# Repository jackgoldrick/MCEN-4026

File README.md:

# MCEN-4026
Manufacturing my pain and suffering

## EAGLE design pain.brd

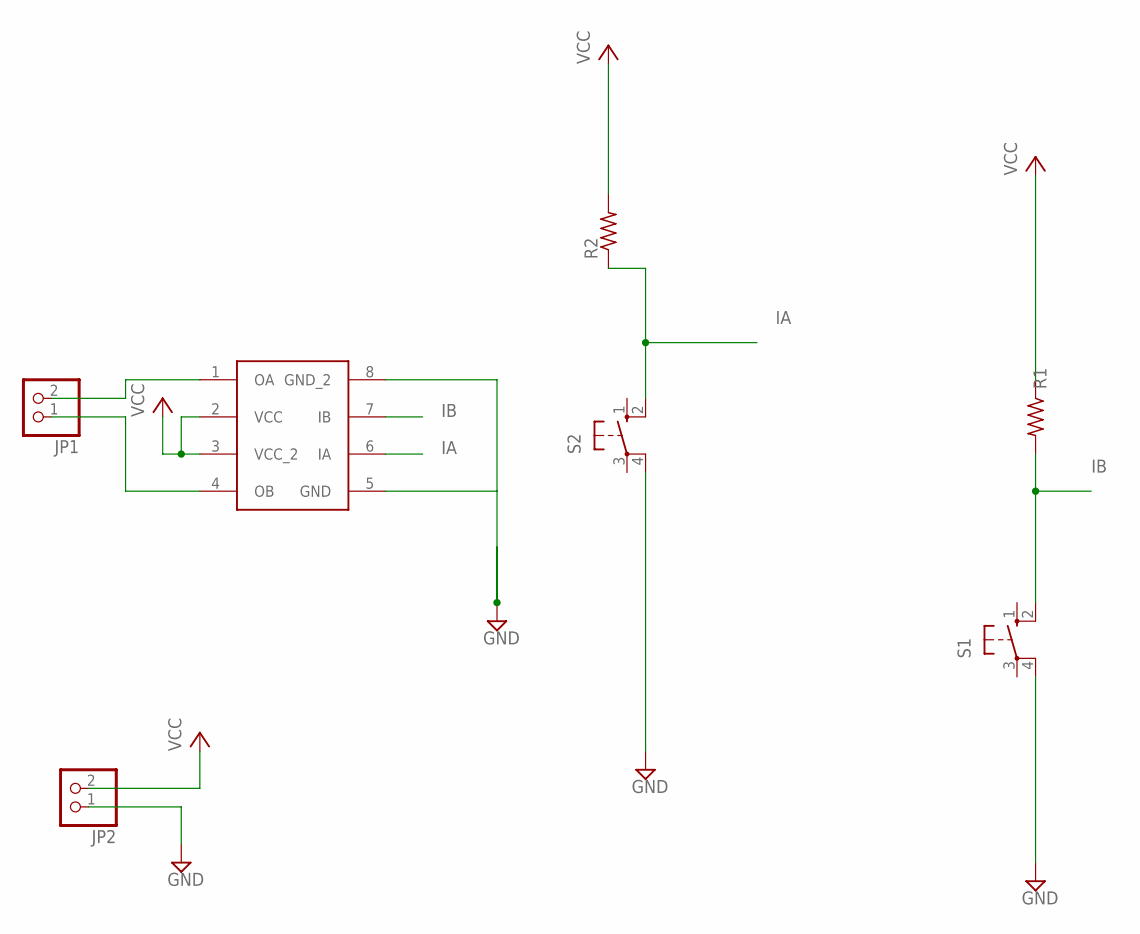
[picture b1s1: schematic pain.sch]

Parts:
JP1, JP2: PINHD-1X2; 1X02
R1, R2: R-US_R0603; R0603
S1, S2: 40-XX; B3F-40XX
U$1: L9110; DIP8

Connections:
GND: JP2.1, S1.4 (P1), S2.4 (P1), U$1.5 (GND), U$1.8 (GND_2)
IA: R2.1, S2.2 (S1), U$1.6 (IA)
IB: R1.2, S1.2 (S1), U$1.7 (IB)
unnamed: JP1.1, U$1.4 (OB)
unnamed: JP1.2, U$1.1 (OA)
VCC: JP2.2, R1.1, R2.2, U$1.2 (VCC), U$1.3 (VCC_2)

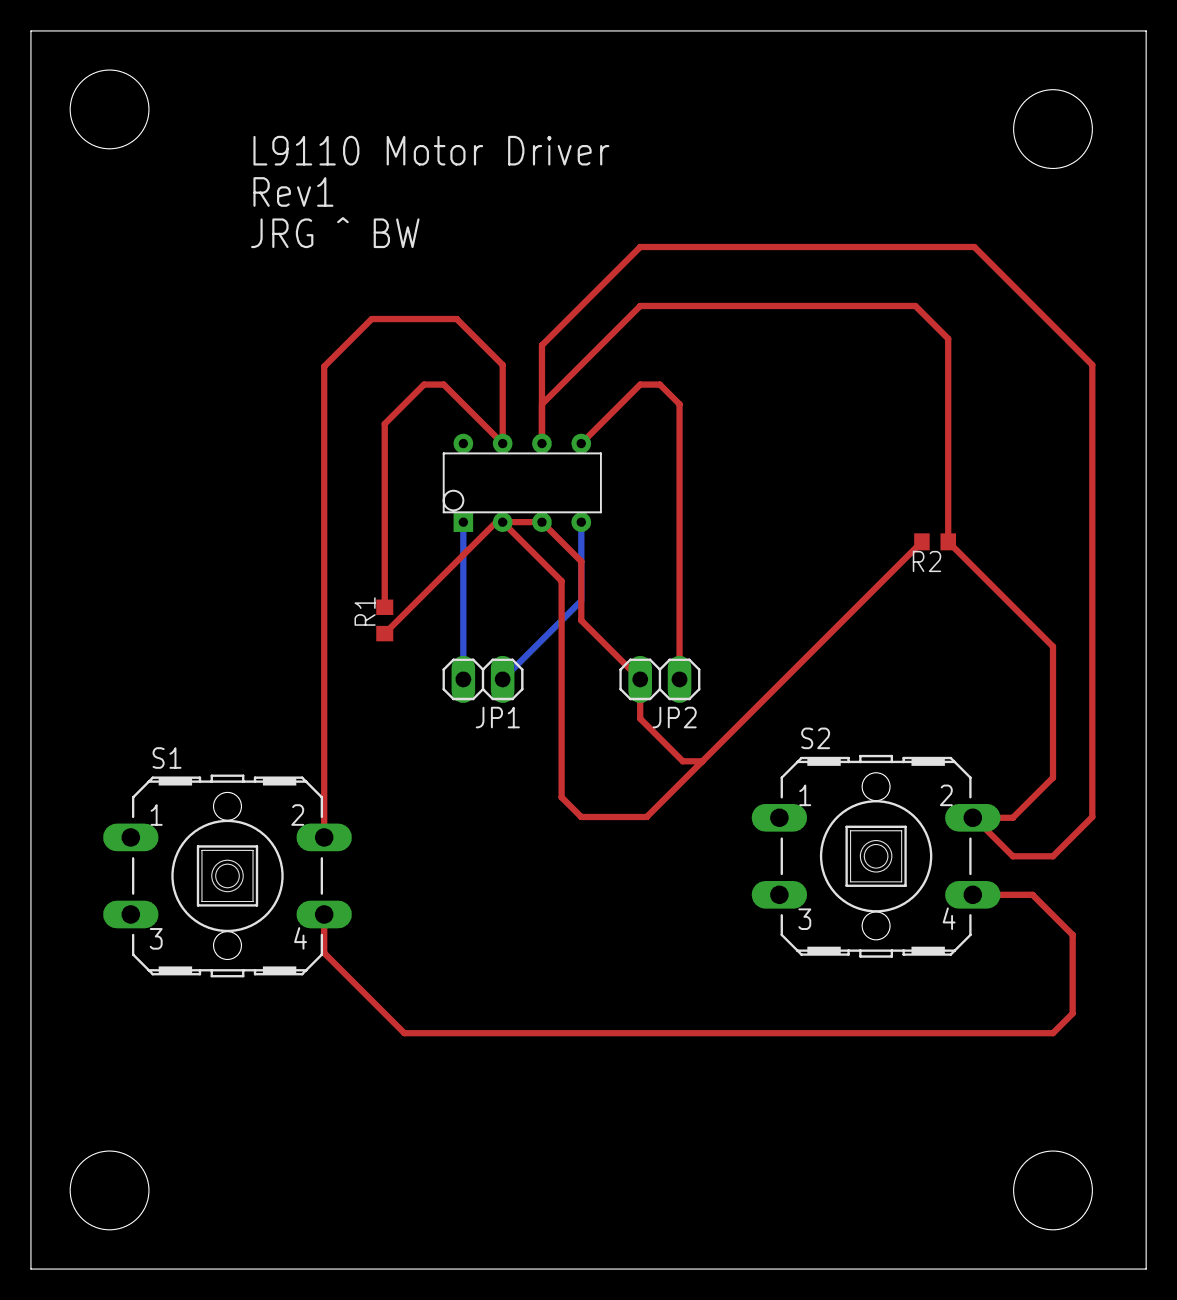
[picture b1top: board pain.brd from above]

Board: 2 copper layers, 72.1 x 80.0 mm, 7 parts (0 on the bottom side), 6 nets.

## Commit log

2024-04-01 init for main
2024-04-03 Lab complete and filled besides a few qs
2024-04-29 PCB add
2024-05-05 end of semester
